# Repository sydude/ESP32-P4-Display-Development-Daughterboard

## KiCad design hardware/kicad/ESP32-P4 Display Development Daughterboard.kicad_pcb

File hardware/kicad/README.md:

# Canonical KiCad project

This directory contains the canonical KiCad project for the ESP32-P4 Displayman Development Daughterboard. The existing project name is preserved.

## Design authority and phase boundary

The committed native three-sheet KiCad hierarchy is the authoritative editable design source. The earlier Python schematic generator is retained only as a blocked historical record: it exits before writing anything, so ordinary KiCad edits cannot diverge from or be overwritten by a second source of truth. The ten unreferenced legacy sheets are documented in `LEGACY_GENERATED_SHEETS.md` and are not part of the active project hierarchy.

The schematic is populated for independent Phase 2 electrical review. The PCB now contains the validated Nano/header datums, the 130 × 100 mm mechanical envelope, all BOM footprints and the pad/net-driven routing-ready component placement documented in `engineering-grade-component-placement.md`. It remains explicitly unrouted: no tracks, copper zones, stackup decision, differential tuning or thermal-via design has begun. The locked, edited/rescaled Waveshare drawing on `User.1` is still a visual working reference rather than production geometry; the validated P1/P2 `F.Fab` datums control the two socket placements.

## Schematic organization

| Page | Sheet | Contents |
|---:|---|---|
| 1 | Root | Three-sheet project hierarchy and review boundary |
| 2 | Power | Protected nominal-12 V input, LM7480-Q1, LM5176-Q1 to `SYS_24V`, LM76003 and TPS25947 Nano feed |
| 3 | Display Power & Backlight | Hold-up, power-fail/sequencing, 1.8/2.8/3.3 V rails, reset gating and TPS922053 backlight driver |
| 4 | Interfaces & Nano | Nano headers/DSI, MIPI ESD and panel connector, touch isolation/ESD and debug/service interfaces |

The post-audit sheets use ordinary-grid pin stubs and explicit net labels. This removes the former fragile near-coincident routes while retaining native editable KiCad symbols and the same hierarchy. The owner may perform a later aesthetic rearrangement, but every such change must preserve the netlist and pass ERC.

## Libraries and portability

- Supported editor/library generation: KiCad 10.
- `Phase2.kicad_sym` is the project-local symbol library.
- `Phase2.pretty` is the project-local footprint library.
- `Phase2.3dshapes` contains project-owned manufacturer or dimension-controlled STEP models.
- Project libraries use `${KIPRJMOD}` and standard KiCad libraries use `${KICAD10_FOOTPRINT_DIR}` / `${KICAD10_3DMODEL_DIR}`. No user-specific absolute path is required.

The project-local footprints and models are committed. A clean checkout with KiCad 10 and its standard footprint/3D packages should open without remapping libraries.

## Verification

The single-source electrical hierarchy was checked with KiCad 10.0.6:

```sh
kicad-cli sch export netlist -o /tmp/phase2.net "hardware/kicad/ESP32-P4 Display Development Daughterboard.kicad_sch"
kicad-cli sch export pdf -o /tmp/phase2.pdf "hardware/kicad/ESP32-P4 Display Development Daughterboard.kicad_sch"
kicad-cli sch erc --severity-all -o hardware/kicad/erc-report.txt "hardware/kicad/ESP32-P4 Display Development Daughterboard.kicad_sch"
```

The committed ERC report records the last native KiCad run before the Nano-header correction: zero messages, errors or warnings, with `endpoint_off_grid` enabled as an error. The subsequent chart-led P1/P2 correction and SSQ metadata change were checked structurally and by explicit connector-pin/net audits in an environment without `kicad-cli`; regenerate the native ERC report and PCB DRC in KiCad 10 before routing authorization. The historical comparison against `cfd665b0` found exactly 25 intentionally removed physical references and the documented rail renames to `SYS_24V`/`SYS24_PGOOD`; that hash is provenance, not the current design baseline.

See `docs/design-notes/maintainability-library-review.md` for the inventory and portability review, `docs/design-notes/project-local-footprint-verification.md` for the completed manufacturer land-pattern audit, `docs/design-notes/mechanical-interface-verification.md` for the original Nano geometry/source validation, `docs/design-notes/preliminary-placement-mechanical-baseline.md` for the SSQ stack/outline baseline, and `docs/design-notes/engineering-grade-component-placement.md` for the routing-ready electrical placement.

## Phase boundary

Engineering-grade placement is complete under owner authorization. Do not begin trace routing, pours, stackup freeze, differential tuning or thermal-via finalization without the next authorization. The sample checks in `preliminary-placement-mechanical-baseline.md` remain prerequisites to mechanical freeze, and the routing gates in `engineering-grade-component-placement.md` apply to the next pass.

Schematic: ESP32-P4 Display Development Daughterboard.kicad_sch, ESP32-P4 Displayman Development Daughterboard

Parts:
C201, C205, C206, C902: 100nF 100V; C_0603_1608Metric
C202: 22uF 50V X7R; C_1210_3225Metric
C203: 100uF 50V; CP_Elec_10x10
C204, C901, C908: 10uF 50V; C_1210_3225Metric
C207: 82nF 100V X7R; C_0603_1608Metric; MPN C0603C823K1RACAUTO
C301: 47pF C0G; C_0402_1005Metric
C302, C305: 270pF C0G; C_0603_1608Metric
C303, C307, C308, C803: 100nF; C_0603_1608Metric
C304: 82nF X7R; C_0603_1608Metric
C306: 1uF 16V; C_0603_1608Metric
C309, C311: 220uF 35V; CP_Elec_10x12.5
C310, C312, C313: 22uF 50V; C_1210_3225Metric
C501: 470nF; C_0603_1608Metric
C502: 2.2uF 10V; C_0603_1608Metric
C503, C513, C514, C603, C801, C903: 1uF 10V; C_0603_1608Metric
C504: 22nF; C_0603_1608Metric
C505, C506: 4.7uF 100V; C_1210_3225Metric
C507: 47nF 100V; C_0603_1608Metric
C508, C509, C510, C511: 22uF 10V; C_1210_3225Metric
C512: 10nF; C_0603_1608Metric
C601: 6800uF 10V; CP_Radial_D16.0mm_P7.50mm; MPN UHW1A682MHD
C602: 100pF C0G; C_0603_1608Metric
C604, C605: 2.2uF 6.3V; C_0603_1608Metric
C606, C802: 4.7uF 6.3V; C_0603_1608Metric
C607: 1nF 50V C0G; C_0603_1608Metric; MPN GRM1885C1H102JA01D
C904: 1nF 50V; C_0603_1608Metric
C905: 2.2uF 50V; C_1210_3225Metric
C906: 1nF; C_0603_1608Metric
C907: 1nF; C_0603_1608Metric; not fitted
D201: SM8S24CA-Q; Bourns_DO-218AB; MPN SM8S24CA-Q
D301, D302: BAT46W-E3-08; D_SOD-123; MPN BAT46W-E3-08
D601: SS34-E3/57T; D_SMA; MPN SS34-E3/57T
D602: 1N4148W; D_SOD-123
D901: SS2H10-E3/52T; D_SMA; MPN SS2H10-E3/52T
D1001, D1002: GREEN; LED_0603_1608Metric; MPN LTST-C191KGKT
F201: 5A TIME DELAY; Fuseholder_Blade_Mini_Keystone_3568; MPN 0297005.WXNV / 3568
FB901: 600R@100MHz 1A; L_0603_1608Metric; MPN BLM18KG601SN1D
J1: 5034802200; CON_5034802200_MOL
J2: 525592253; CON_525592253_MOL
J101: ESP32-P4-WIFI6-DB-P1; 1x20
J102: ESP32-P4-WIFI6-DB-P2; 1x20
J201: VEHICLE 12V; CONN_SD-43045-007_02_MOL; MPN 43045-0218
J501: SERVICE LINK 5V; SolderJumper-2_P1.3mm_Bridged_RoundedPad1.0x1.5mm
J702: DISPLAYMAN LCD 40P; Molex_CON_5051104096; MPN 505110-4096
J801: Wurth 8pin Top Contact FPC; Wurth_68710814022
J901: BL HARD DISABLE; PinHeader_1x02_P2.54mm_Vertical
L201: 2.2uH 8A; L_Bourns_SRP1038A_10.0x10.0mm; MPN SRP1038A-2R2M
L301: 15uH; L_Coilcraft_XAL7070-XXX; MPN XAL7070-153MEC
L501: 10uH; L_Coilcraft_XAL7070-XXX; MPN XAL7070-103MEC
L901: 68uH; L_Vishay_IHLP-6767; MPN IHLP6767GZER680M11
PWR101, PWR201, PWR301, PWR501, PWR601: PWR_FLAG
Q201, Q202, Q301, Q302, Q303, Q304: CSD19531Q5A; Texas_DQJ0008A_VSONP-8; MPN CSD19531Q5A
Q801: MMBT3904; SOT-23; MPN MMBT3904LT1G
R201: 1.0R 2W; R_2512_6332Metric
R202: 56.2k 1%; R_0603_1608Metric
R203: 10.0k 1%; R_0603_1608Metric
R204: 100k 1%; R_0603_1608Metric
R205: 6.49k 1%; R_0603_1608Metric
R206: 100R 1%; R_0603_1608Metric; MPN ERJ-3EKF1000V
R301: 20mR 1% 2W; R_2512_6332Metric
R302, R309: 100R; R_0402_1005Metric
R303: 27.4k 1%; R_0603_1608Metric
R304: 93.1k 1%; R_0603_1608Metric
R305: 15.0k 1%; R_0603_1608Metric
R306: 580k 1%; R_0603_1608Metric
R307: 20.0k 1%; R_0603_1608Metric
R308, R509, R510, R604, R606, R607, R608, R609, R908: 47k; R_0603_1608Metric
R501: 100k 0.1%; R_0603_1608Metric
R502: 24.9k 0.1%; R_0603_1608Metric
R503, R602: 1.00M 1%; R_0603_1608Metric
R504: 68.1k 1%; R_0603_1608Metric
R505: 549R 1%; R_0603_1608Metric; not fitted
R506: 1.05k 1%; R_0603_1608Metric
R507, R511, R512, R611, R801, R802, R804, R909, R1001, R1002, R1003, R1004: 100k; R_0603_1608Metric
R508: 26.7k; R_0603_1608Metric
R601: 3.3R 2W PULSE; R_2512_6332Metric
R603: 21.5k 1%; R_0603_1608Metric
R605, R610, R1006: 10k; R_0603_1608Metric
R701, R702, R703, R704, R705, R706: 0R 0201; R_0201_0603Metric
R803: 4.7k; R_0603_1608Metric
R901, R902: 1.65R 0.1%; R_1206_3216Metric
R903, R905: 100R; R_0603_1608Metric
R904: 83k 1%; R_0603_1608Metric
R906: 0R; R_0603_1608Metric
R907: 1.00M; R_0603_1608Metric; not fitted
R910: 0R LED CURRENT LINK; R_2512_6332Metric
R1005: 47k; R_0603_1608Metric; not fitted
R1007: 2.2k; R_0603_1608Metric
U201: LM74800QDRRRQ1; Texas_DRR0012E_WSON-12_3x3mm_P0.5mm_EP1.3x2.5mm; MPN LM74800QDRRRQ1
U301: LM5176QPWPRQ1; Texas_PWP0028V_TSSOP-28-1EP_4.4x9.7mm_P0.65mm_EP3.4x9.7mm_M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; MPN LM5176QPWPRQ1
U501: LM76003RNPR; Texas_RNP0030B_WQFN-30-1EP_4x6mm_P0.5mm_EP1.8x4.5mm_Thermal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; MPN LM76003RNPR
U502: TPS259470ARPWR; RPW0010A-MFG; MPN TPS259470ARPWR
U601: TPS3808G01DBVR; SOT-23-6; MPN TPS3808G01DBVR
U602: LM3880MF-1AA/NOPB; SOT-23-6; MPN LM3880MF-1AA/NOPB
U603: TLV75518PDBVR; SOT-23-5; MPN TLV75518PDBVR
U604: TLV75528PDBVR; SOT-23-5; MPN TLV75528PDBVR
U605: TPS22919DCKR; SOT-363_SC-70-6; MPN TPS22919DCKR
U606, U607, U608: SN74LVC1G07DBVR; SOT-23-5; MPN SN74LVC1G07DBVR
U701: TPD6E05U06RVZR; Texas_R-PUSON-N14; MPN TPD6E05U06RVZR
U801: TLV75533PDBVR; SOT-23-5; MPN TLV75533PDBVR
U802: TMUX1574PWR; TSSOP-16_4.4x5mm_P0.65mm; MPN TMUX1574PWR
U803: TPD4E05U06DQAR; USON-10_2.5x1.0mm_P0.5mm; MPN TPD4E05U06DQAR
U901: TPS922053DYYR; Texas_DYY0014A_TSOT-23-14; MPN TPS922053DYYR
U902: SN74LVC1G11DCKR; SOT-363_SC-70-6; MPN SN74LVC1G11DCKR

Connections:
BL_DIM: J901.2, R909.1, U901.6 (EN/PWM)
BL_FAULT_N: R908.1, U901.7 (FAULT_N)
BL_GATE_OK: J901.1, U902.4 (Y)
BL_PWM: J101.10 (GPIO23), R1003.1, U902.1 (A)
BL_SW: D901.2 (A), L901.1, U901.14 (SW)
BOOT1: C307.1, D301.1 (K), U301.26 (BOOT1)
BOOT2: C308.1, D302.1 (K), U301.20 (BOOT2)
BUCK_SHUNT_HI: Q302.1 (S), Q302.2 (S), Q302.3 (S), R301.1, R302.1
BUS_SENSE: C607.1, R602.2, R603.1, U601.5 (SENSE)
COMP_RC: C304.1, R305.2
CTP_INT: J801.6 (INT), R803.1, U802.11 (S3A), U803.4 (D2+)
CTP_INT_HOST: J101.15 (GPIO32), R1005.1, U802.9 (D3)
CTP_RESET_N: J801.7 (RST_N), R804.1, U802.14 (S4A), U803.5 (D2-)
CTP_RESET_N_HOST: J101.9 (GPIO22), R1004.1, U802.12 (D4)
CTP_SCL: J801.4 (SCL), U802.2 (S1A), U803.1 (D1+)
CTP_SDA: J801.5 (SDA), U802.5 (S2A), U803.2 (D1-)
DISP_HOLD_5V: C601.1, C603.1, PWR601.1, R601.2, R604.2, R607.2, R608.2, R609.2, U601.3 (MR_N), U601.6 (VDD), U602.1 (VCC), U603.1 (IN), U604.1 (IN)
DSI_CLK_N_SRC: J1.15, R705.1
DSI_CLK_P_SRC: J1.14, R706.1
DSI_D0_N_SRC: J1.21, R701.1
DSI_D0_P_SRC: J1.20, R702.1
DSI_D1_N_SRC: J1.18, R703.1
DSI_D1_P_SRC: J1.17, R704.1
EFUSE_DVDT: C512.1, U502.7 (DVDT)
EFUSE_EN: R511.2, R512.1, U502.1 (EN/UVLO)
EFUSE_ILM: R505.1, R506.1, U502.9 (ILM)
EFUSE_OV: R507.2, R508.1, U502.2 (OVLO)
GND: C201.2, C202.2, C203.2, C204.2, C206.2, C207.2, C302.2, C303.2, C304.2, C305.2, C306.2, C309.2, C310.2, C311.2, C312.2, C313.2, C502.2, C503.2, C504.2, C505.2, C506.2, C507.2, C508.2, C509.2, C510.2, C511.2, C512.2, C513.2, C514.2, C601.2, C602.2, C603.2, C604.2, C605.2, C606.2, C607.2, C801.2, C802.2, C803.2, C901.2, C902.2, C903.2, C906.2, C907.2, C908.2, D201.2 (A), J1.4, J1.7, J1.10, J1.13, J1.16, J1.19, J1.22, J101.3 (GND), J101.8 (GND), J101.13 (GND), J101.18 (GND), J102.3 (GND), J102.8 (GND), J102.13 (GND), J102.16 (SCL/GPIO8), J102.18 (GND), J201.2 (BATT-), J702.4 (GND), J702.7 (GND), J702.10 (GND), J702.13 (GND), J702.16 (GND), J702.17 (GND), J702.18 (GND), J702.19 (GND), J702.20 (GND), J702.21 (GND), J702.22 (GND), J702.25 (GND), J702.30 (GND), J801.1 (GND), J801.8 (GND), PWR101.1, Q304.1 (S), Q304.2 (S), Q304.3 (S), Q801.2 (E), R203.2, R205.2, R301.2, R303.2, R304.2, R307.2, R309.1, R502.2, R504.2, R505.2, R506.2, R508.2, R512.2, R603.2, R606.2, R611.2, R804.2, R904.2, R907.2, R909.2, R1001.2, R1002.2, R1003.2, R1004.2, R1005.2, R1006.2, R1007.2, U201.7 (GND), U301.5 (DITH), U301.10 (AGND), U301.22 (PGND), U301.29 (EP), U501.7 (NC_GND), U501.13 (AGND), U501.14 (AGND), U501.15 (AGND), U501.17 (SYNC/MODE), U501.19 (NC_GND), U501.23 (NC_GND), U501.24 (PGND), U501.25 (PGND), U501.26 (PGND), U501.27 (NC_GND), U501.28 (NC_GND), U501.29 (NC_GND), U501.30 (NC_GND), U501.31 (EP), U502.8 (GND), U601.2 (GND), U602.2 (GND), U603.2 (GND), U604.2 (GND), U605.2 (GND), U606.3 (GND), U607.3 (GND), U608.3 (GND), U701.5 (GND), U701.10 (GND), U801.2 (GND), U802.1 (SEL), U802.3 (S1B), U802.6 (S2B), U802.8 (GND), U802.10 (S3B), U802.13 (S4B), U803.3 (GND), U803.8 (GND), U901.1 (PGND), U901.2 (AGND), U901.8 (TEMP), U902.3 (GND)
HDRV1: Q301.4 (G), U301.27 (HDRV1)
HDRV2: Q303.4 (G), U301.19 (HDRV2)
HOLD_CHARGE: D601.1 (K), R601.1
HOST_3V3_DETECT: Q801.1 (B), R801.2
HOST_3V3_REF: J1.1, R801.1
HOST_5V: J101.2 (VSYS), J501.2
HOST_5V_EFUSED: C514.1, J501.1, U502.6 (OUT)
HOST_EFUSE_FLT: R509.1, U502.4 (FLT)
HOST_I2C_SCL: J1.3, U802.4 (D1)
HOST_I2C_SDA: J1.2, U802.7 (D2)
LCD_IOVCC: C604.1, J702.3 (IOVCC_1V8), R610.1, U603.5 (OUT), U606.5 (VCC), U607.5 (VCC), U608.5 (VCC)
LCD_PWR_EN: J101.6 (GPIO20), R605.1, R1001.1
LCD_RESET_CMD_N: J101.7 (GPIO21), R1002.1, U606.2 (A)
LCD_RESET_N: J702.5 (RESET_N), R610.2, R611.1, U606.4 (Y_OD), U607.4 (Y_OD), U608.4 (Y_OD)
LCD_VCI: C606.1, J702.2 (VCI_2V8), U605.5 (QOD), U605.6 (VOUT)
LCD_VCI_RAW: C605.1, U604.5 (OUT), U605.1 (VIN)
LDRV1: Q302.4 (G), U301.25 (LDRV1)
LDRV2: Q304.4 (G), U301.21 (LDRV2)
LED5_R: D1002.1 (K), R1007.1
LED24_R: D1001.1 (K), R1006.1
LED_A: C905.1, C908.1, FB901.2, J702.39 (LED+), J702.40 (LED+)
LED_K: C905.2, J702.31 (LED-), J702.32 (LED-), R906.1, R910.1
LED_K_RAW: R901.1, R902.1, R903.1, R910.2
LED_SENSE_N: C904.2, L901.2, R901.2, R902.2, U901.13 (CSN)
LM760_BOOT: C501.1, U501.6 (BOOT)
LM760_EN: R503.2, R504.1, U501.18 (EN)
LM760_FB: R501.2, R502.1, U501.12 (FB)
LM760_SS: C504.1, U501.11 (SS/TRK)
LM760_SW: C501.2, L501.1, U501.1 (SW), U501.2 (SW), U501.3 (SW), U501.4 (SW), U501.5 (SW)
LM760_VCC: C502.1, U501.8 (VCC)
LM5176_COMP: C305.1, R305.1, U301.9 (COMP)
LM5176_CS: C301.1, R302.2, U301.16 (CS)
LM5176_CSG: C301.2, R309.2, U301.15 (CSG)
LM5176_MODE: R304.1, U301.4 (MODE)
LM5176_RT: R303.1, U301.6 (RT/SYNC)
LM5176_SLOPE: C302.1, U301.7 (SLOPE)
LM5176_SS: C303.1, U301.8 (SS)
LM5176_VCC: C306.1, D301.2 (A), D302.2 (A), U301.23 (VCC)
MIPI_0N: J702.8 (MIPI_0N), R701.2, U701.14 (D1+)
MIPI_0P: J702.9 (MIPI_0P), R702.2, U701.13 (D1-)
MIPI_1N: J702.11 (MIPI_1N), R703.2, U701.12 (D2+)
MIPI_1P: J702.12 (MIPI_1P), R704.2, U701.11 (D2-)
MIPI_CLKN: J702.14 (MIPI_CLKN), R705.2, U701.9 (D3+)
MIPI_CLKP: J702.15 (MIPI_CLKP), R706.2, U701.8 (D3-)
unnamed: U301.13 (ISNS-), U301.14 (ISNS+)
SEQ_ENABLE: D602.2 (A), R605.2, R606.1, U602.3 (EN)
SEQ_FLAG1: R607.1, U602.6 (FLAG1), U603.3 (EN), U604.3 (EN)
SEQ_FLAG2: R608.1, U602.5 (FLAG2), U605.3 (ON)
SEQ_FLAG3: R609.1, U602.4 (FLAG3), U607.2 (A), U902.2 (B)
SW1: C307.2, L301.1, Q301.1 (S), Q301.2 (S), Q301.3 (S), Q302.5 (D), Q302.6 (D), Q302.7 (D), Q302.8 (D), U301.28 (SW1)
SW2: C308.2, L301.2, Q303.1 (S), Q303.2 (S), Q303.3 (S), Q304.5 (D), Q304.6 (D), Q304.7 (D), Q304.8 (D), U301.18 (SW2)
SYS5_PGOOD: R510.1, U501.16 (PGOOD)
SYS24_PGOOD: R308.1, U301.17 (PGOOD)
SYS_5V_3A: C503.1, C508.1, C509.1, C510.1, C511.1, C513.1, C801.1, D601.2 (A), D1002.2 (A), L501.2, PWR501.1, R308.2, R501.1, R507.1, R509.2, R510.2, R511.1, U501.9 (BIAS), U502.5 (IN), U801.1 (IN)
SYS_24V: C311.1, C312.1, C313.1, C505.1, C506.1, C507.1, C901.1, C902.1, D901.1 (K), D1001.2 (A), FB901.1, PWR301.1, Q303.5 (D), Q303.6 (D), Q303.7 (D), Q303.8 (D), R306.1, R503.1, R602.1, U301.12 (VOSNS), U301.24 (BIAS), U501.20 (PVIN), U501.21 (PVIN), U501.22 (PVIN), U901.3 (VIN)
TMUX_EN_N: Q801.3 (C), R802.1, U802.15 (EN_N)
TOUCH_3V3: C802.1, C803.1, J801.3 (VDD_3V3), R802.2, R803.2, U801.5 (OUT), U802.16 (VDD), U902.6 (VCC)
TPS922_COMP: C906.1, R905.1, U901.10 (COMP)
TPS922_COMP_C: C907.1, R905.2
TPS922_CSP: C904.1, R903.2, U901.12 (CSP)
TPS922_FSET: R904.1, U901.9 (FSET)
TPS922_UVP: R906.2, R907.1, U901.11 (UVP)
TPS922_VCC: C903.1, R908.2, U901.4 (VCC), U901.5 (ADIM/HD)
TPS3808_CT: C602.1, U601.4 (CT)
VEH_12V_RAW: F201.1, J201.1 (BATT+)
VEH_CAP: C205.1, U201.11 (CAP)
VEH_DAMP: C204.1, R201.2
VEH_DGATE: Q201.4 (G), U201.1 (DGATE)
VEH_FB: R306.2, R307.1, U301.11 (FB)
VEH_FET_MID: C205.2, C206.1, Q201.5 (D), Q201.6 (D), Q201.7 (D), Q201.8 (D), Q202.5 (D), Q202.6 (D), Q202.7 (D), Q202.8 (D), U201.10 (VS), U201.12 (C)
VEH_FILTER: C201.1, C202.1, D201.1 (K), L201.2, Q201.1 (S), Q201.2 (S), Q201.3 (S), R201.1, R202.1, U201.2 (A), U201.3 (VSNS)
VEH_FUSED: F201.2, L201.1
VEH_HGATE: Q202.4 (G), R206.1, U201.8 (HGATE)
VEH_HGATE_DVDT: C207.1, R206.2
VEH_OV: R204.2, R205.1, U201.5 (OV)
VEH_OV_TOP: R204.1, U201.4 (SW)
VEH_PROT: C203.1, C309.1, C310.1, PWR201.1, Q202.1 (S), Q202.2 (S), Q202.3 (S), Q301.5 (D), Q301.6 (D), Q301.7 (D), Q301.8 (D), U201.9 (OUT), U301.1 (EN/UVLO), U301.2 (VIN), U301.3 (VISNS)
VEH_UVLO: R202.2, R203.1, U201.6 (EN/UVLO)
VIN_GOOD: D602.1 (K), R604.1, U601.1 (RESET_N), U608.2 (A), U801.3 (EN), U902.5 (C)

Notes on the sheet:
Target: 24.0 V, 30 W continuous, 300 kHz. RFB 580k/20k gives 24.0 V nominal.
01: SINGLE 12 V INPUT
02: VEHICLE INPUT PROTECTION
SYSTEM 24 V DISTRIBUTION (DEPRECATED)
LM76003: 500 kHz, 10 uH; checked over the regulated SYS_24V range. 4x22 uF output bank.
06: DISPLAY RAILS AND SEQUENCING
OV divider 100k/6.49k: 20.18 V nominal cutoff; rejects accidental 24 V vehicle-port connection.
83k FSET selects 300 kHz. 68 uH is validated over the regulated SYS_24V range; see calculations.
09: 240 MA BACKLIGHT
6800 uF is isolated from Host/backlight. At 0.20 A for 30 ms, droop is 0.88 V; sequencing remains above LDO dropout.
F101/TVS coordination and adapter inrush are prototype verification items; no automotive qualification claim.
UVLO divider 56.2k/10.0k: 8.15 V rising, about 7.49 V falling using LM7480 thresholds.
03: LM5176 SINGLE-SOURCE BUCK-BOOST
P1 pins 2/4 are Host 5 V. GPIO21/P1-13 is an unconnected documented alternate. GPIO24 remains untouched for USB Serial/JTAG.
At 8 V/30 W/85%, Iavg=4.41 A. With 15 uH, ripple is about 1.19 App and peak about 5.00 A.
05: SYSTEM 5 V AND HOST FEED
TMUX1574 SEL=0 uses the A paths; all B paths are grounded per datasheet. EN_N is pulled high when Host 3.3 V is absent.
Two 1.65 ohm/0.1% resistors in parallel give 0.825 ohm: 242.4 mA nominal; +3% threshold gives 249.9 mA.
07: MIPI DSI AND LCD CONNECTOR
100k/24.9k feedback gives 5.016 V nominal. 22 nF SS gives approximately 11 ms ramp.
TPS3808 threshold: 0.405*(1M+21.5k)/21.5k = 19.23 V nominal. Its reset directly clamps sequence/reset/backlight validity.
LM5176 output directly supplies SYS_24V; no high-voltage source ORing is present.
Host I2C already has 2.2k pull-ups; no additional Host-side pull-ups. Touch INT has the vendor-required 4.7k pull-up.
08: GT9271 TOUCH INTERFACE
Bench development uses a regulated/current-limited nominal 12 V supply at J201.
R701–R706 are inline zero-ohm 0201 tuning locations; layout them as minimal-discontinuity pass-through pads.
Straight-through lane identity and polarity. No AC coupling, common-mode choke, probe pad, or branch.
Corrected P1 controls: pin 7 GPIO23 BL PWM; 13 GPIO20 LCD power; 15 GPIO21 LCD reset; 16 GPIO22 touch reset; 23 GPIO32 touch INT.
10: HOST HEADERS AND DEBUG
SYS_24V has 264 uF converter output capacitance plus 19.547 uF distributed local bypass.

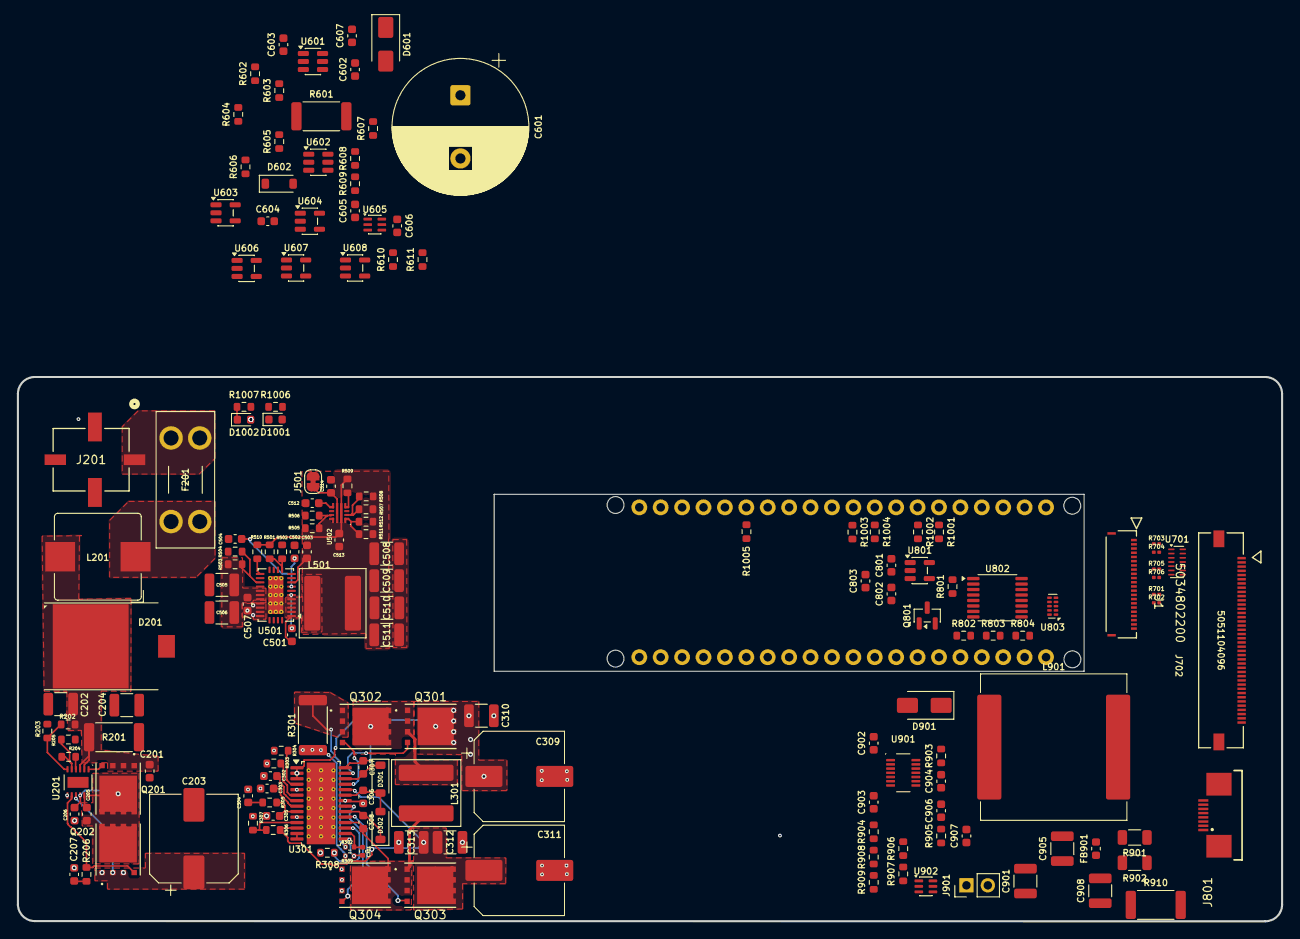
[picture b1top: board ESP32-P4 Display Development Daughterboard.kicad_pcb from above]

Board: 4 copper layers, 150.0 x 64.6 mm, 164 parts (0 on the bottom side), 107 nets.

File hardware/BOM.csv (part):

Reference,Value,Manufacturer,MPN,Footprint,DNP,Sheet,Description
C201,100nF 100V,,,Capacitor_SMD:C_0603_1608Metric,POP,Power,
C202,22uF 50V X7R,,,Capacitor_SMD:C_1210_3225Metric,POP,Power,
C203,100uF 50V,,,Capacitor_SMD:CP_Elec_10x10,POP,Power,
C204,10uF 50V,,,Capacitor_SMD:C_1210_3225Metric,POP,Power,
C205,100nF 100V,,,Capacitor_SMD:C_0603_1608Metric,POP,Power,
C206,100nF 100V,,,Capacitor_SMD:C_0603_1608Metric,POP,Power,
C207,82nF 25V X7R,KEMET,C0603C823K3RACTU,Capacitor_SMD:C_0603_1608Metric,POP,Power,LM74800 HGATE dV/dt inrush-control capacitor
C301,47pF C0G,,,Capacitor_SMD:C_0402_1005Metric,POP,Power,
C302,270pF C0G,,,Capacitor_SMD:C_0603_1608Metric,POP,Power,
C303,100nF,,,Capacitor_SMD:C_0603_1608Metric,POP,Power,
C304,82nF X7R,,,Capacitor_SMD:C_0603_1608Metric,POP,Power,
C305,270pF C0G,,,Capacitor_SMD:C_0603_1608Metric,POP,Power,
C306,1uF 16V,,,Capacitor_SMD:C_0603_1608Metric,POP,Power,
C307,100nF,,,Capacitor_SMD:C_0603_1608Metric,POP,Power,
C308,100nF,,,Capacitor_SMD:C_0603_1608Metric,POP,Power,
C309,220uF 35V,,,Capacitor_SMD:CP_Elec_10x12.5,POP,Power,
C310,22uF 50V,,,Capacitor_SMD:C_1210_3225Metric,POP,Power,
C311,220uF 35V,,,Capacitor_SMD:CP_Elec_10x12.5,POP,Power,
C312,22uF 50V,,,Capacitor_SMD:C_1210_3225Metric,POP,Power,
C313,22uF 50V,,,Capacitor_SMD:C_1210_3225Metric,POP,Power,
C501,470nF,,,Capacitor_SMD:C_0603_1608Metric,POP,Power,
C502,2.2uF 10V,,,Capacitor_SMD:C_0603_1608Metric,POP,Power,
C503,1uF 10V,,,Capacitor_SMD:C_0603_1608Metric,POP,Power,
C504,22nF,,,Capacitor_SMD:C_0603_1608Metric,POP,Power,
C505,4.7uF 100V,,,Capacitor_SMD:C_1210_3225Metric,POP,Power,
C506,4.7uF 100V,,,Capacitor_SMD:C_1210_3225Metric,POP,Power,
C507,47nF 100V,,,Capacitor_SMD:C_0603_1608Metric,POP,Power,
C508,22uF 10V,,,Capacitor_SMD:C_1210_3225Metric,POP,Power,
C509,22uF 10V,,,Capacitor_SMD:C_1210_3225Metric,POP,Power,
C510,22uF 10V,,,Capacitor_SMD:C_1210_3225Metric,POP,Power,
C511,22uF 10V,,,Capacitor_SMD:C_1210_3225Metric,POP,Power,
C512,10nF,,,Capacitor_SMD:C_0603_1608Metric,POP,Power,About 5 ms 5 V output rise
C513,1uF 10V,,,Capacitor_SMD:C_0603_1608Metric,POP,Power,Local TPS25947 input bypass
C514,1uF 10V,,,Capacitor_SMD:C_0603_1608Metric,POP,Power,Local TPS25947 controlled output capacitance
C601,6800uF 10V,Nichicon,UHW1A682MHD,Capacitor_THT:CP_Radial_D16.0mm_P7.50mm,POP,Display Power & Backlight,"Display-only hard-unplug hold-up; 16x25 mm, 7.5 mm pitch"
C602,100pF C0G,,,Capacitor_SMD:C_0603_1608Metric,POP,Display Power & Backlight,
C603,1uF 10V,,,Capacitor_SMD:C_0603_1608Metric,POP,Display Power & Backlight,
C604,2.2uF 6.3V,,,Capacitor_SMD:C_0603_1608Metric,POP,Display Power & Backlight,
C605,2.2uF 6.3V,,,Capacitor_SMD:C_0603_1608Metric,POP,Display Power & Backlight,
C606,4.7uF 6.3V,,,Capacitor_SMD:C_0603_1608Metric,POP,Display Power & Backlight,
C607,1nF 50V C0G,Murata,GRM1885C1H102JA01D,Capacitor_SMD:C_0603_1608Metric,POP,Display Power & Backlight,TPS3808 SENSE bypass; place at U601 SENSE/GND
C801,1uF 10V,,,Capacitor_SMD:C_0603_1608Metric,POP,Interfaces & Nano,
C802,4.7uF 6.3V,,,Capacitor_SMD:C_0603_1608Metric,POP,Interfaces & Nano,
C803,100nF,,,Capacitor_SMD:C_0603_1608Metric,POP,Interfaces & Nano,
C901,10uF 50V,,,Capacitor_SMD:C_1210_3225Metric,POP,Display Power & Backlight,
C902,100nF 100V,,,Capacitor_SMD:C_0603_1608Metric,POP,Display Power & Backlight,
C903,1uF 10V,,,Capacitor_SMD:C_0603_1608Metric,POP,Display Power & Backlight,
C904,1nF 50V,,,Capacitor_SMD:C_0603_1608Metric,POP,Display Power & Backlight,
C905,2.2uF 50V,,,Capacitor_SMD:C_1210_3225Metric,POP,Display Power & Backlight,LED ripple capacitor across the module string
C906,1nF,,,Capacitor_SMD:C_0603_1608Metric,POP,Display Power & Backlight,
C907,1nF,,,Capacitor_SMD:C_0603_1608Metric,DNP,Display Power & Backlight,DNP alternate series compensation branch
C908,10uF 50V,,,Capacitor_SMD:C_1210_3225Metric,POP,Display Power & Backlight,
D201,SM8S24CA-Q,Bourns,SM8S24CA-Q,Phase2:Bourns_DO-218AB,POP,Power,6.6 kW bidirectional vehicle TVS
D301,BAT46W-E3-08,Vishay,BAT46W-E3-08,Diode_SMD:D_SOD-123,POP,Power,100 V Schottky bootstrap diode for buck-side high gate
D302,BAT46W-E3-08,Vishay,BAT46W-E3-08,Diode_SMD:D_SOD-123,POP,Power,100 V Schottky bootstrap diode for boost-side high gate
D601,SS34-E3/57T,Vishay,SS34-E3/57T,Diode_SMD:D_SMA,POP,Display Power & Backlight,Hold-up reverse isolation
D602,1N4148W,,,Diode_SMD:D_SOD-123,POP,Display Power & Backlight,VIN_GOOD clamps sequencer enable low on bus failure
D901,SS2H10-E3/52T,Vishay,SS2H10-E3/52T,Diode_SMD:D_SMA,POP,Display Power & Backlight,100 V 2 A Schottky catch diode
D1001,GREEN,Lite-On,LTST-C191KGKT,LED_SMD:LED_0603_1608Metric,POP,Interfaces & Nano,
D1002,GREEN,Lite-On,LTST-C191KGKT,LED_SMD:LED_0603_1608Metric,POP,Interfaces & Nano,
F201,5A TIME DELAY,Littelfuse / Keystone,0297005.WXNV / 3568,Fuse:Fuseholder_Blade_Mini_Keystone_3568,POP,Power,5 A MINI blade fuse in Keystone 3568 holder
FB901,600R@100MHz 1A,Murata,BLM18KG601SN1D,Inductor_SMD:L_0603_1608Metric,POP,Display Power & Backlight,Panel LED anode EMI bead; verify DC loss/headroom
J201,VEHICLE 12V,Molex,43045-0218,Phase2:Molex_Micro-Fit_3.0_43045-0218_2x01-1MP_P3.00mm_Vertical,POP,Power,2-circuit vertical Micro-Fit 3.0 SMT header; sealing not claimed
J501,SERVICE LINK 5V,,,Jumper:SolderJumper-2_P1.3mm_Bridged_RoundedPad1.0x1.5mm,POP,Power,Normally closed service/current-measure disconnect
J701,NANO DSI 15P,Amphenol ICC,SFW15R-2STE1LF,Phase2:Amphenol_SFW15R-2STE1LF,POP,Interfaces & Nano,Nano-facing top-contact provisional connector
J702,DISPLAYMAN LCD 40P,Molex,505110-4096,Phase2:Molex_505110-4096,POP,Interfaces & Nano,Exact Displayman-specified bottom-contact panel connector
J801,GT9271 TOUCH 8P,Hirose,FH12-8S-0.5SH(55),Connector_FFC-FPC:Hirose_FH12-8S-0.5SH_1x08-1MP_P0.50mm_Horizontal,POP,Interfaces & Nano,Bottom-contact touch FPC connector
J901,BL HARD DISABLE,,,Connector_PinHeader_2.54mm:PinHeader_1x02_P2.54mm_Vertical,POP,Display Power & Backlight,Normally fitted hardware backlight disable shunt
J1001,SSQ-113-01-G-D,Samtec,SSQ-113-01-G-D,Phase2:Samtec_SSQ-113-01-G-D_BottomMount,POP,Interfaces & Nano,"Bottom-mounted P1 electrical stack socket; 2x13, 2.54 mm, 8.51 mm body, 2.64 mm tail, 20 uin gold contact"
J1002,SSQ-113-01-G-D,Samtec,SSQ-113-01-G-D,Phase2:Samtec_SSQ-113-01-G-D_BottomMount,POP,Interfaces & Nano,Bottom-mounted electrically unused P2 alignment socket; structural loads carried by standoffs
J1003,DEBUG HEADER,Samtec,TSW-105-07-G-D,Connector_PinHeader_2.54mm:PinHeader_2x05_P2.54mm_Vertical,POP,Interfaces & Nano,Low-speed development/debug access
L201,2.2uH 8A,Bourns,SRP1038A-2R2M,Phase2:L_Bourns_SRP1038A_10.0x10.0mm,POP,Power,Shielded AEC-Q200 input filter inductor
L301,15uH,Coilcraft,XAL7070-153MEC,Inductor_SMD:L_Coilcraft_XAL7070-XXX,POP,Power,Shielded AEC-Q200 buck-boost inductor; 10.1 A saturation rating
L501,10uH,Coilcraft,XAL7070-103MEC,Inductor_SMD:L_Coilcraft_XAL7070-XXX,POP,Power,Isat >=5.5 A shielded inductor
L901,68uH,Vishay,IHLP6767GZER680M11,Inductor_SMD:L_Vishay_IHLP-6767,POP,Display Power & Backlight,Shielded 68 uH LED buck inductor; 6.1 A heat-rated / 4.5 A saturation typical
Q201,CSD19531Q5A,Texas Instruments,CSD19531Q5A,Package_SON:Texas_DQK,POP,Power,100 V N-channel MOSFET
Q202,CSD19531Q5A,Texas Instruments,CSD19531Q5A,Package_SON:Texas_DQK,POP,Power,100 V N-channel MOSFET
Q301,CSD19531Q5A,Texas Instruments,CSD19531Q5A,Package_SON:Texas_DQK,POP,Power,100 V N-channel MOSFET
Q302,CSD19531Q5A,Texas Instruments,CSD19531Q5A,Package_SON:Texas_DQK,POP,Power,100 V N-channel MOSFET
Q303,CSD19531Q5A,Texas Instruments,CSD19531Q5A,Package_SON:Texas_DQK,POP,Power,100 V N-channel MOSFET
Q304,CSD19531Q5A,Texas Instruments,CSD19531Q5A,Package_SON:Texas_DQK,POP,Power,100 V N-channel MOSFET
Q801,MMBT3904,onsemi,MMBT3904LT1G,Package_TO_SOT_SMD:SOT-23,POP,Interfaces & Nano,Nano-powered detector: isolation enabled only when Nano 3.3 V exists
R201,1.0R 2W,,,Resistor_SMD:R_2512_6332Metric,POP,Power,Series damping leg
R202,56.2k 1%,,,Resistor_SMD:R_0603_1608Metric,POP,Power,
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
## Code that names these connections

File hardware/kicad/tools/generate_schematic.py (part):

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
def tlv755(ref, value, out, enable, x, y):
    return ic(ref, value, "Package_TO_SOT_SMD:SOT-23-5", "https://www.ti.com/lit/ds/symlink/tlv755p.pdf", [
        pin(1, "IN", "power_in", "DISP_HOLD_5V" if out.startswith("LCD_") else "SYS_5V_3A"),
        pin(2, "GND", "power_in", "GND"), pin(3, "EN", "input", enable),
        pin(4, "NC", "no_connect", None, "R"), pin(5, "OUT", "power_out", out, "R")], x, y,
        description=f"500 mA fixed LDO for {out}")
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        passive("C201", "100nF 100V", "Capacitor_SMD:C_0603_1608Metric", "VEH_FILTER", "GND", 70, 75),
        passive("C202", "22uF 50V X7R", "Capacitor_SMD:C_1210_3225Metric", "VEH_FILTER", "GND", 110, 35),
        passive("C203", "100uF 50V", "Capacitor_SMD:CP_Elec_10x10", "VEH_FILTER", "GND", 110, 55),
        passive("R201", "1.0R 2W", "Resistor_SMD:R_2512_6332Metric", "VEH_FILTER", "VEH_DAMP", 110, 75, description="Series damping leg"),
        passive("C204", "10uF 50V", "Capacitor_SMD:C_1210_3225Metric", "VEH_DAMP", "GND", 150, 35),
        diode("D201", "SM8S24CA-Q", "Phase2:Bourns_DO-218AB", "VEH_FILTER", "GND", 150, 55, mpn="SM8S24CA-Q", manufacturer="Bourns", description="6.6 kW bidirectional vehicle TVS"),
        ic("U201", "LM74800QDRRRQ1", "Phase2:Texas_DRR0012A_WSON-12_3x3mm_P0.5mm_EP1.2x2.5mm", "https://www.ti.com/lit/ds/symlink/lm7480-q1.pdf", [
            pin(1, "DGATE", "output", "VEH_DGATE"), pin(2, "A", "input", "VEH_FILTER"), pin(3, "VSNS", "input", "VEH_FILTER"),
            pin(4, "SW", "input", "VEH_OV_TOP"), pin(5, "OV", "input", "VEH_OV"), pin(6, "EN/UVLO", "input", "VEH_UVLO"),
            pin(7, "GND", "power_in", "GND", "R"), pin(8, "HGATE", "output", "VEH_HGATE", "R"),
            pin(9, "OUT", "input", "VEH_PROT", "R"), pin(10, "VS", "power_in", "VEH_FET_MID", "R"),
            pin(11, "CAP", "power_out", "VEH_CAP", "R"), pin(12, "C", "input", "VEH_FET_MID", "R"),
            pin(13, "RTN_EP", "no_connect", None, "R")], 205, 55,
            description="Reverse-battery, ideal-diode, OV and back-to-back disconnect controller"),
        mosfet("Q201", "VEH_FILTER", "VEH_DGATE", "VEH_FET_MID", 255, 35),
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
    # 03 - 30 W LM5176 buck-boost.
    lm5176_pins = [
        pin(1, "EN/UVLO", "input", "VEH_PROT"), pin(2, "VIN", "power_in", "VEH_PROT"), pin(3, "VISNS", "input", "VEH_PROT"),
        pin(4, "MODE", "input", "LM5176_MODE"), pin(5, "DITH", "input", "GND"), pin(6, "RT/SYNC", "input", "LM5176_RT"),
        pin(7, "SLOPE", "input", "LM5176_SLOPE"), pin(8, "SS", "input", "LM5176_SS"), pin(9, "COMP", "output", "LM5176_COMP"),
        pin(10, "AGND", "power_in", "GND"), pin(11, "FB", "input", "VEH_FB"), pin(12, "VOSNS", "input", "VEH_24V"),
        pin(13, "ISNS-", "input", "VEH_24V", "R"), pin(14, "ISNS+", "input", "VEH_24V", "R"),
        pin(15, "CSG", "input", "LM5176_CSG", "R"), pin(16, "CS", "input", "LM5176_CS", "R"),
        pin(17, "PGOOD", "open_collector", "VEH_PGOOD", "R"), pin(18, "SW2", "passive", "SW2", "R"),
        pin(19, "HDRV2", "output", "HDRV2", "R"), pin(20, "BOOT2", "passive", "BOOT2", "R"),
        pin(21, "LDRV2", "output", "LDRV2", "R"), pin(22, "PGND", "power_in", "GND", "R"),
        pin(23, "VCC", "power_out", "LM5176_VCC", "R"), pin(24, "BIAS", "power_in", "VEH_24V", "R"),
        pin(25, "LDRV1", "output", "LDRV1", "R"), pin(26, "BOOT1", "passive", "BOOT1", "R"),
        pin(27, "HDRV1", "output", "HDRV1", "R"), pin(28, "SW1", "passive", "SW1", "R"),
        pin(29, "EP", "power_in", "GND", "R"),
    ]
    p = [ic("U301", "LM5176QPWPRQ1", "Phase2:Texas_PWP0029_HTSSOP-28-EP", "https://www.ti.com/lit/ds/symlink/lm5176-q1.pdf", lm5176_pins, 90, 85,
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
    # 05 - LM76003 and TPS25947 Nano feed.
    p = [ic("U501", "LM76003RNPR", "Package_DFN_QFN:Texas_RNP0030B_WQFN-30-1EP_4x6mm_P0.5mm_EP1.8x4.5mm_ThermalVias", "https://www.ti.com/lit/ds/symlink/lm76003.pdf", [
            pin(1, "SW", "power_out", "LM760_SW"), pin(2, "SW", "passive", "LM760_SW"), pin(3, "SW", "passive", "LM760_SW"),
            pin(4, "SW", "passive", "LM760_SW"), pin(5, "SW", "passive", "LM760_SW"), pin(6, "BOOT", "passive", "LM760_BOOT"),
            pin(7, "NC_GND", "passive", "GND"), pin(8, "VCC", "power_out", "LM760_VCC"),
            pin(9, "BIAS", "power_in", "SYS_5V_3A"), pin(10, "RT", "input", None), pin(11, "SS/TRK", "input", "LM760_SS"),
            pin(12, "FB", "input", "LM760_FB"), pin(13, "AGND", "power_in", "GND"), pin(14, "AGND", "passive", "GND"),
            pin(15, "AGND", "passive", "GND"), pin(16, "PGOOD", "open_collector", "SYS5_PGOOD", "R"),
            pin(17, "SYNC/MODE", "input", "GND", "R"), pin(18, "EN", "input", "LM760_EN", "R"), pin(19, "NC_GND", "passive", "GND", "R"),
            pin(20, "PVIN", "power_in", "VIN_PROT_24V", "R"), pin(21, "PVIN", "passive", "VIN_PROT_24V", "R"),
            pin(22, "PVIN", "passive", "VIN_PROT_24V", "R"), pin(23, "NC_GND", "passive", "GND", "R"),
            pin(24, "PGND", "power_in", "GND", "R"), pin(25, "PGND", "passive", "GND", "R"), pin(26, "PGND", "passive", "GND", "R"),
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         passive("C510", "22uF 10V", "Capacitor_SMD:C_1210_3225Metric", "SYS_5V_3A", "GND", 305, 75),
         passive("C511", "22uF 10V", "Capacitor_SMD:C_1210_3225Metric", "SYS_5V_3A", "GND", 305, 95),
         ic("U502", "TPS259470ARPWR", "Phase2:Texas_RPW0010A_HotRod_QFN-10_2x2mm_P0.45mm", "https://www.ti.com/lit/ds/symlink/tps25947.pdf", [
             pin(1, "EN/UVLO", "input", "EFUSE_EN"), pin(2, "OVLO", "input", "EFUSE_OV"), pin(3, "AUXOFF", "no_connect", None),
             pin(4, "FLT", "open_collector", "NANO_EFUSE_FLT"), pin(5, "IN", "power_in", "SYS_5V_3A"),
             pin(6, "OUT", "power_out", "NANO_5V_EFUSED", "R"), pin(7, "DVDT", "output", "EFUSE_DVDT", "R"),
             pin(8, "GND", "power_in", "GND", "R"), pin(9, "ILM", "output", "EFUSE_ILM", "R"), pin(10, "ITIMER", "no_connect", None, "R")], 365, 70,
             description="True reverse-current blocking Nano feed eFuse"),
         passive("R505", "549R 1%", "Resistor_SMD:R_0603_1608Metric", "EFUSE_ILM", "GND", 430, 35, description="DNP 6.07 A laboratory option only", dnp=True),
         passive("R506", "1.05k 1%", "Resistor_SMD:R_0603_1608Metric", "EFUSE_ILM", "GND", 430, 55, description="Populated current limit resistor: about 3.18 A"),
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         passive("R601", "3.3R 2W PULSE", "Resistor_SMD:R_2512_6332Metric", "HOLD_CHARGE", "DISP_HOLD_5V", 45, 55, description="Hold-up capacitor inrush limiter, about 1.4 A initial"),
         passive("C601", "6800uF 10V", "Phase2:CP_Elec_6800uF_10V", "DISP_HOLD_5V", "GND", 45, 75, description="Display-only hard-unplug hold-up; body size frozen before PCB placement"),
         ic("U601", "TPS3808G01DBVR", "Package_TO_SOT_SMD:SOT-23-6", "https://www.ti.com/lit/ds/symlink/tps3808.pdf", [
             pin(1, "RESET_N", "open_collector", "VIN_GOOD"), pin(2, "GND", "power_in", "GND"), pin(3, "MR_N", "input", "DISP_HOLD_5V"),
             pin(4, "CT", "input", "TPS3808_CT", "R"), pin(5, "SENSE", "input", "BUS_SENSE", "R"), pin(6, "VDD", "power_in", "DISP_HOLD_5V", "R")], 100, 55,
             description="Early common-bus failure supervisor"),
         passive("R602", "1.00M 1%", "Resistor_SMD:R_0603_1608Metric", "VIN_PROT_24V", "BUS_SENSE", 155, 35),
         passive("R603", "21.5k 1%", "Resistor_SMD:R_0603_1608Metric", "BUS_SENSE", "GND", 155, 55),
         passive("C602", "100pF C0G", "Capacitor_SMD:C_0603_1608Metric", "TPS3808_CT", "GND", 155, 75),
         passive("R604", "47k", "Resistor_SMD:R_0603_1608Metric", "VIN_GOOD", "DISP_HOLD_5V", 155, 95),
         ic("U602", "LM3880MF-1AA/NOPB", "Package_TO_SOT_SMD:SOT-23-6", "https://www.ti.com/lit/ds/symlink/lm3880.pdf", [
             pin(1, "VCC", "power_in", "DISP_HOLD_5V"), pin(2, "GND", "power_in", "GND"), pin(3, "EN", "input", "SEQ_ENABLE"),
             pin(4, "FLAG3", "open_collector", "SEQ_FLAG3", "R"), pin(5, "FLAG2", "open_collector", "SEQ_FLAG2", "R"), pin(6, "FLAG1", "open_collector", "SEQ_FLAG1", "R")], 215, 55,
             description="10 ms 1-2-3 / 3-2-1 rail sequencer"),
         passive("R605", "10k", "Resistor_SMD:R_0603_1608Metric", "LCD_PWR_EN", "SEQ_ENABLE", 270, 35),
         passive("R606", "47k", "Resistor_SMD:R_0603_1608Metric", "SEQ_ENABLE", "GND", 270, 55),
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         tlv755("U603", "TLV75518PDBVR", "LCD_IOVCC", "SEQ_FLAG1", 325, 80),
         tlv755("U604", "TLV75528PDBVR", "LCD_VCI_RAW", "SEQ_FLAG1", 385, 40),
         ic("U605", "TPS22919DCKR", "Package_TO_SOT_SMD:SOT-363_SC-70-6", "https://www.ti.com/lit/ds/symlink/tps22919.pdf", [
             pin(1, "VIN", "power_in", "LCD_VCI_RAW"), pin(2, "GND", "power_in", "GND"), pin(3, "ON", "input", "SEQ_FLAG2"),
             pin(4, "NC", "no_connect", None, "R"), pin(5, "QOD", "passive", "LCD_VCI", "R"),
             pin(6, "VOUT", "power_out", "LCD_VCI", "R")], 385, 80,
             description="VCI sequenced load switch with quick output discharge"),
         passive("C603", "1uF 10V", "Capacitor_SMD:C_0603_1608Metric", "DISP_HOLD_5V", "GND", 445, 35),
         passive("C604", "2.2uF 6.3V", "Capacitor_SMD:C_0603_1608Metric", "LCD_IOVCC", "GND", 445, 55),
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

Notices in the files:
hardware/kicad/ESP32-P4 Display Development Daughterboard.kicad_sch:
© 2026 Sy Aryeh
Hardware license: see LICENSE.md
